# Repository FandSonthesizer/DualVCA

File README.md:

# DualVCA
I created this pcb as a building block for the developement of guitar pedals. It works quite nice and is easy to build.
As usual I put the two vactrols together from white LED's and LDR's (LDR 03) with some electric tape.

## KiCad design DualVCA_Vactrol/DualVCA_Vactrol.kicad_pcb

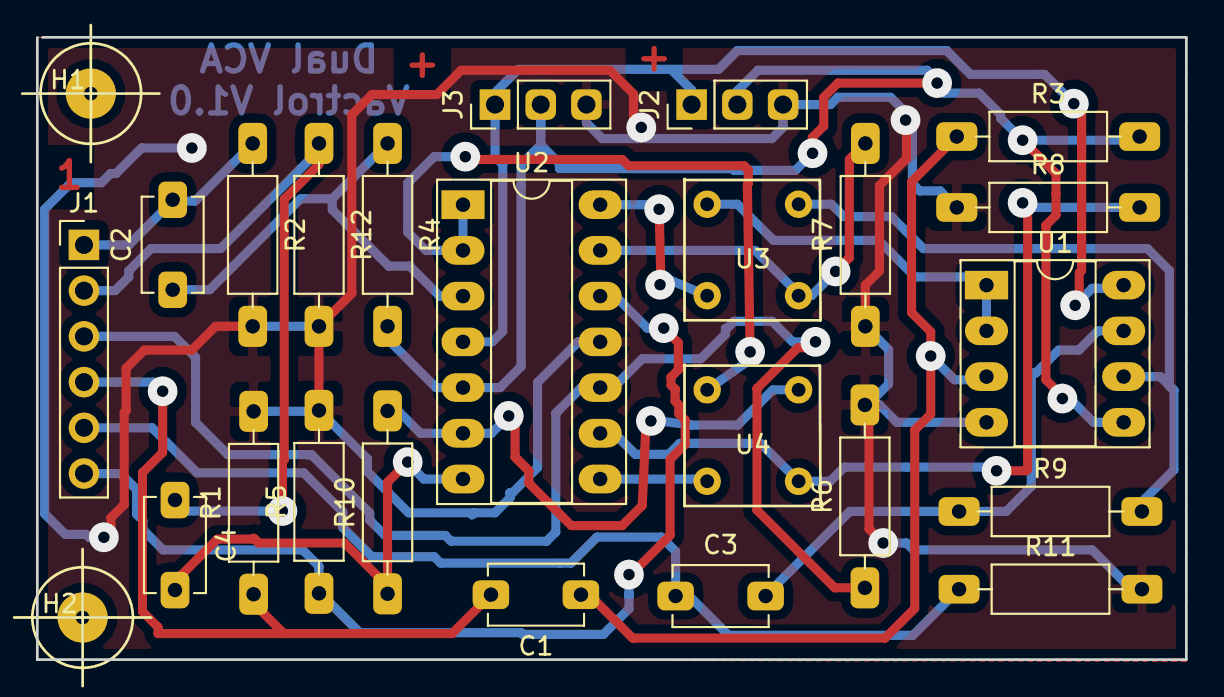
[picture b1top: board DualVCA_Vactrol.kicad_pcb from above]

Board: 2 copper layers, 63.8 x 34.6 mm, 25 parts (0 on the bottom side), 21 nets.

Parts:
C1, C2, C3, C4: 220n; Kondensator_Keramik
H1, H2: MountingHole; MountHole
J1: VCA; PinHeader_1x06_P2.54mm_Vertical
J2: PowerIn; Stift_0x3
J3: PowerOut; Stift_0x3
R1, R2, R5, R6, R11, R12: 1M; Widerstand_liegend
R3, R4: 330k; Widerstand_liegend
R7, R8: 1,6k; Widerstand_liegend
R9, R10: 5,6k; Widerstand_liegend
U1: TL072; DIP-8_W7.62mm_Socket_LongPads
U2: TL074; DIP-14_W7.62mm_Socket_LongPads
U3, U4: Vactrol

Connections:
+9V: J2.1, J3.1, U1.8, U2.4
AudioIn: C2.2, J1.1, R2.1
AudioIn2: C1.2, J1.4, R1.1
AudioOut: C4.1, J1.2, R12.1
AudioOut2: C3.1, J1.5, R11.1
CVIn: J1.3, R6.1, U2.10
CVIn2: J1.6, R5.1, U2.12
GND: J2.3, J3.3, R1.2, R2.2, R5.2, R6.2, R7.1, R8.1, R11.2, R12.2, U1.4, U2.11
unnamed: C1.1, R3.1, U1.3
unnamed: C2.1, R4.1, U2.3
unnamed: C3.2, R9.1, U1.7
unnamed: C4.2, R10.1, U2.7
unnamed: R7.2, U2.13, U3.4
unnamed: R8.2, U2.9, U4.4
unnamed: R9.2, U1.6, U3.2
unnamed: R10.2, U2.6, U4.2
unnamed: U1.1, U1.2, U3.1
unnamed: U2.1, U2.2, U4.1
unnamed: U2.8, U4.3
unnamed: U2.14, U3.3
Vref: J2.2, J3.2, R3.2, R4.2, U1.5, U2.5
